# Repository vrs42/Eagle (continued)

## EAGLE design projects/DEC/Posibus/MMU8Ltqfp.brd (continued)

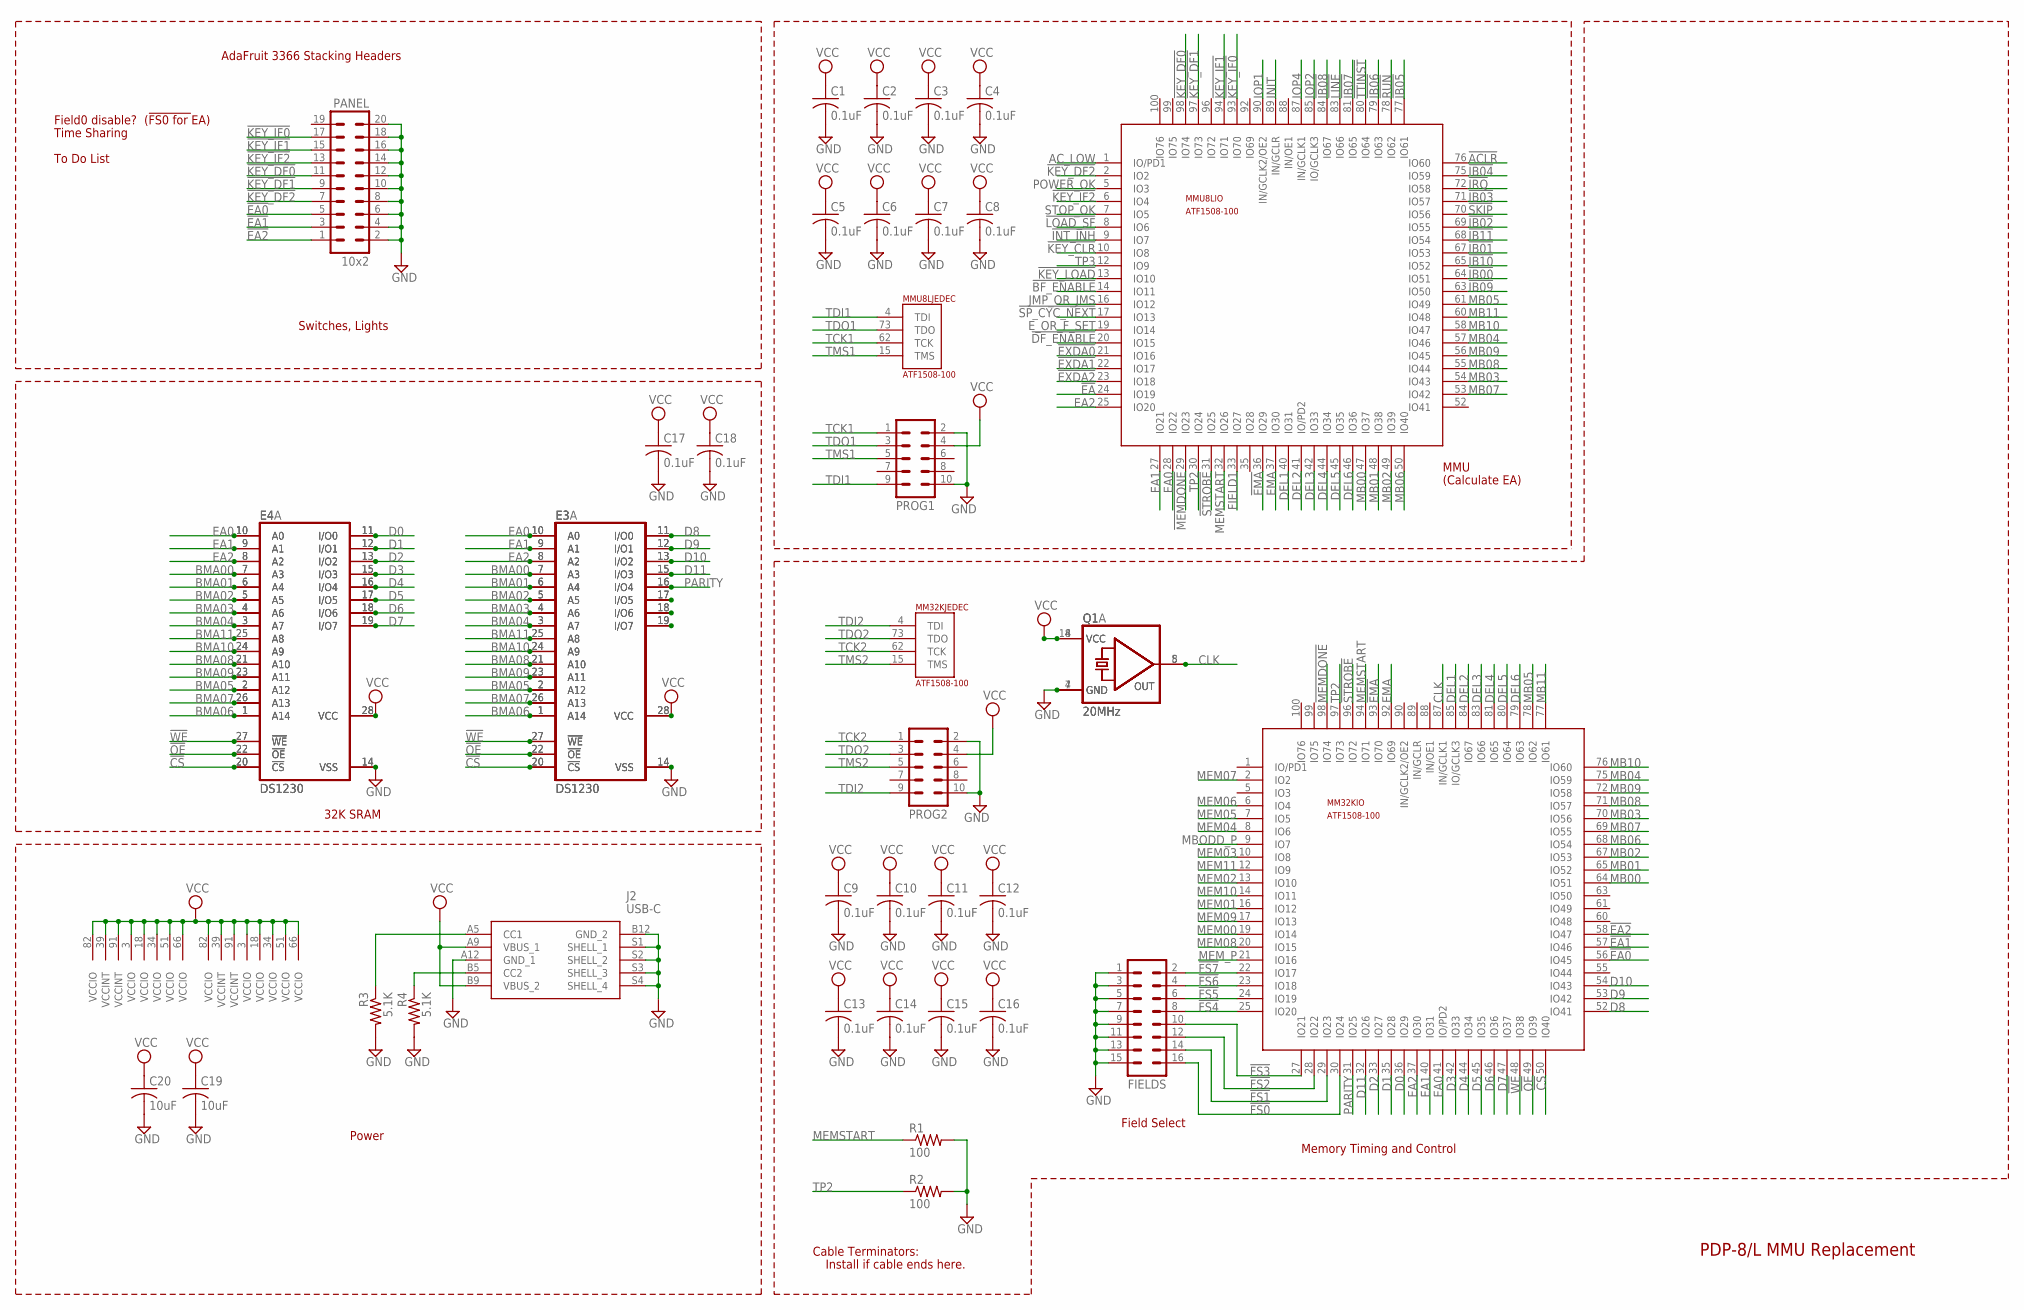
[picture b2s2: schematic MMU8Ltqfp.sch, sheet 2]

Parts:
C1, C2, C3, C4, C5, C6, C7, C8, C9, C10, C11, C12, C13, C14, C15, C16, C17, C18: 0.1uF; C0805
C19, C20: 10uF; C0805
E3, E4: DS1230; DIL28-6
E3A, E4A: DS1230; DIL28-3
FIELDS: MA08-2
J2: USB-C; USB497000A
MM32K: ATF1508-100; TQFP-100
MMU8L: ATF1508-100; TQFP-100
PANEL: 10x2; MA10-2
PROG1, PROG2: ML10
Q1: 20MHz; DIL14S
Q1A: 20MHz; DIL08S
R1, R2: 100; R1206
R3, R4: 5.1K; R0805

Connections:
!ACLR: MMU8L.76 (IO60); also elsewhere on the board
!BF_ENABLE: MMU8L.14 (IO11); also elsewhere on the board
!CS: E3.20 (!CS), E3A.20 (!CS), E4.20 (!CS), E4A.20 (!CS), MM32K.50 (IO40)
!DF_ENABLE: MMU8L.20 (IO15); also elsewhere on the board
!EA: MMU8L.24 (IO19); also elsewhere on the board
!EA0: MM32K.56 (IO45), PANEL.5
!EA1: MM32K.57 (IO46), PANEL.3
!EA2: MM32K.58 (IO47), PANEL.1
!EMA: MM32K.93 (IO70), MMU8L.36 (IO29); also elsewhere on the board
!EXDA0: MMU8L.21 (IO16); also elsewhere on the board
!EXDA1: MMU8L.22 (IO17); also elsewhere on the board
!EXDA2: MMU8L.23 (IO18); also elsewhere on the board
!FS0: FIELDS.16, MM32K.30 (IO24)
!FS1: FIELDS.14, MM32K.29 (IO23)
!FS2: FIELDS.12, MM32K.28 (IO22)
!FS3: FIELDS.10, MM32K.27 (IO21)
!FS4: FIELDS.8, MM32K.25 (IO20)
!FS5: FIELDS.6, MM32K.24 (IO19)
!FS6: FIELDS.4, MM32K.23 (IO18)
!FS7: FIELDS.2, MM32K.22 (IO17)
!IB00: MMU8L.64 (IO51); also elsewhere on the board
!IB01: MMU8L.67 (IO53); also elsewhere on the board
!IB02: MMU8L.69 (IO55); also elsewhere on the board
!IB03: MMU8L.71 (IO57); also elsewhere on the board
!IB04: MMU8L.75 (IO59); also elsewhere on the board
!IB05: MMU8L.77 (IO61); also elsewhere on the board
!IB06: MMU8L.79 (IO63); also elsewhere on the board
!IB07: MMU8L.81 (IO65); also elsewhere on the board
!IB08: MMU8L.84 (IO67); also elsewhere on the board
!IB09: MMU8L.63 (IO50); also elsewhere on the board
!IB10: MMU8L.65 (IO52); also elsewhere on the board
!IB11: MMU8L.68 (IO54); also elsewhere on the board
!INT_INH: MMU8L.9 (IO7); also elsewhere on the board
!IRQ: MMU8L.72 (IO58); also elsewhere on the board
!KEY_CLR: MMU8L.10 (IO8); also elsewhere on the board
!KEY_DF0: MMU8L.98 (IO74), PANEL.11
!KEY_DF1: MMU8L.97 (IO73), PANEL.9
!KEY_DF2: MMU8L.2 (IO2), PANEL.7; also elsewhere on the board
!KEY_IF0: MMU8L.93 (IO70), PANEL.17
!KEY_IF1: MMU8L.94 (IO71), PANEL.15
!KEY_IF2: MMU8L.6 (IO4), PANEL.13; also elsewhere on the board
!KEY_LOAD: MMU8L.13 (IO10); also elsewhere on the board
!LINE: MMU8L.83 (IO66); also elsewhere on the board
!LOAD_SF: MMU8L.8 (IO6); also elsewhere on the board
!MEMDONE: MM32K.98 (IO74), MMU8L.29 (IO23); also elsewhere on the board
!OE: E3.22 (!OE), E3A.22 (!OE), E4.22 (!OE), E4A.22 (!OE), MM32K.49 (IO39)
!RUN: MMU8L.78 (IO62); also elsewhere on the board
!SKIP: MMU8L.70 (IO56); also elsewhere on the board
!SP_CYC_NEXT: MMU8L.17 (IO13); also elsewhere on the board
!STROBE: MM32K.96 (IO72), MMU8L.31 (IO25); also elsewhere on the board
!TTINST: MMU8L.80 (IO64); also elsewhere on the board
!WE: E3.27 (!WE), E3A.27 (!WE), E4.27 (!WE), E4A.27 (!WE), MM32K.48 (IO38)
AC_LOW: MMU8L.1 (IO/PD1); also elsewhere on the board
BMA00: E3.7 (A3), E3A.7 (A3), E4.7 (A3), E4A.7 (A3); also elsewhere on the board
BMA01: E3.6 (A4), E3A.6 (A4), E4.6 (A4), E4A.6 (A4); also elsewhere on the board
BMA02: E3.5 (A5), E3A.5 (A5), E4.5 (A5), E4A.5 (A5); also elsewhere on the board
BMA03: E3.4 (A6), E3A.4 (A6), E4.4 (A6), E4A.4 (A6); also elsewhere on the board
BMA04: E3.3 (A7), E3A.3 (A7), E4.3 (A7), E4A.3 (A7); also elsewhere on the board
BMA05: E3.2 (A12), E3A.2 (A12), E4.2 (A12), E4A.2 (A12); also elsewhere on the board
BMA06: E3.1 (A14), E3A.1 (A14), E4.1 (A14), E4A.1 (A14); also elsewhere on the board
BMA07: E3.26 (A13), E3A.26 (A13), E4.26 (A13), E4A.26 (A13); also elsewhere on the board
BMA08: E3.21 (A10), E3A.21 (A10), E4.21 (A10), E4A.21 (A10); also elsewhere on the board
BMA09: E3.23 (A11), E3A.23 (A11), E4.23 (A11), E4A.23 (A11); also elsewhere on the board
BMA10: E3.24 (A9), E3A.24 (A9), E4.24 (A9), E4A.24 (A9); also elsewhere on the board
BMA11: E3.25 (A8), E3A.25 (A8), E4.25 (A8), E4A.25 (A8); also elsewhere on the board
CLK: MM32K.87 (IN/GCLK1), Q1.8 (OUT), Q1A.5 (OUT)
D0: E4.11 (I/O0), E4A.11 (I/O0), MM32K.36 (IO29)
D1: E4.12 (I/O1), E4A.12 (I/O1), MM32K.35 (IO28)
D2: E4.13 (I/O2), E4A.13 (I/O2), MM32K.33 (IO27)
D3: E4.15 (I/O3), E4A.15 (I/O3), MM32K.42 (IO33)
D4: E4.16 (I/O4), E4A.16 (I/O4), MM32K.44 (IO34)
D5: E4.17 (I/O5), E4A.17 (I/O5), MM32K.45 (IO35)
D6: E4.18 (I/O6), E4A.18 (I/O6), MM32K.46 (IO36)
D7: E4.19 (I/O7), E4A.19 (I/O7), MM32K.47 (IO37)
D8: E3.11 (I/O0), E3A.11 (I/O0), MM32K.52 (IO41)
D9: E3.12 (I/O1), E3A.12 (I/O1), MM32K.53 (IO42)
D10: E3.13 (I/O2), E3A.13 (I/O2), MM32K.54 (IO43)
D11: E3.15 (I/O3), E3A.15 (I/O3), MM32K.32 (IO26)
DEL1: MM32K.85 (IO/GCLK3), MMU8L.40 (IO31)
DEL2: MM32K.84 (IO67), MMU8L.41 (IO/PD2)
DEL3: MM32K.83 (IO66), MMU8L.42 (IO33)
DEL4: MM32K.81 (IO65), MMU8L.44 (IO34)
DEL5: MM32K.80 (IO64), MMU8L.45 (IO35)
DEL6: MM32K.79 (IO63), MMU8L.46 (IO36)
EA0: E3.10 (A0), E3A.10 (A0), E4.10 (A0), E4A.10 (A0), MM32K.41 (IO/PD2), MMU8L.28 (IO22)
EA1: E3.9 (A1), E3A.9 (A1), E4.9 (A1), E4A.9 (A1), MM32K.40 (IO31), MMU8L.27 (IO21)
EA2: E3.8 (A2), E3A.8 (A2), E4.8 (A2), E4A.8 (A2), MM32K.37 (IO30), MMU8L.25 (IO20)
EMA: MM32K.92 (IO69), MMU8L.37 (IO30); also elsewhere on the board
E_OR_F_SET: MMU8L.19 (IO14); also elsewhere on the board
FIELD1: MMU8L.33 (IO27); also elsewhere on the board
GND: C1.2, C2.2, C3.2, C4.2, C5.2, C6.2, C7.2, C8.2, C9.2, C10.2, C11.2, C12.2, C13.2, C14.2, C15.2, C16.2, C17.2, C18.2, C19.2, C20.2, E3.14 (VSS), E3A.14 (VSS), E4.14 (VSS), E4A.14 (VSS), FIELDS.1, FIELDS.3, FIELDS.5, FIELDS.7, FIELDS.9, FIELDS.11, FIELDS.13, FIELDS.15, J2.A12 (GND_1), J2.B12 (GND_2), J2.S1 (SHELL_1), J2.S2 (SHELL_2), J2.S3 (SHELL_3), J2.S4 (SHELL_4), MM32K.11 (GND), MM32K.26 (GND), MM32K.38 (GND), MM32K.43 (GND), MM32K.59 (GND), MM32K.74 (GND), MM32K.86 (GND), MM32K.95 (GND), MMU8L.11 (GND), MMU8L.26 (GND), MMU8L.38 (GND), MMU8L.43 (GND), MMU8L.59 (GND), MMU8L.74 (GND), MMU8L.86 (GND), MMU8L.95 (GND), PANEL.2, PANEL.4, PANEL.6, PANEL.8, PANEL.10, PANEL.12, PANEL.14, PANEL.16, PANEL.18, PANEL.20, PROG1.2, PROG1.10, PROG2.2, PROG2.10, Q1.7 (GND), Q1A.4 (GND), R1.2, R2.2, R3.2, R4.2; also elsewhere on the board
INIT: MMU8L.89 (IN/GCLR); also elsewhere on the board
IOP1: MMU8L.90 (IN/GCLK2/OE2); also elsewhere on the board
IOP2: MMU8L.85 (IO/GCLK3); also elsewhere on the board
IOP4: MMU8L.87 (IN/GCLK1); also elsewhere on the board
JMP_OR_JMS: MMU8L.16 (IO12); also elsewhere on the board
MB00: MM32K.64 (IO51), MMU8L.47 (IO37); also elsewhere on the board
MB01: MM32K.65 (IO52), MMU8L.48 (IO38); also elsewhere on the board
MB02: MM32K.67 (IO53), MMU8L.49 (IO39); also elsewhere on the board
MB03: MM32K.70 (IO56), MMU8L.54 (IO43); also elsewhere on the board
MB04: MM32K.75 (IO59), MMU8L.57 (IO46); also elsewhere on the board
MB05: MM32K.78 (IO62), MMU8L.61 (IO49); also elsewhere on the board
MB06: MM32K.68 (IO54), MMU8L.50 (IO40); also elsewhere on the board
MB07: MM32K.69 (IO55), MMU8L.53 (IO42); also elsewhere on the board
MB08: MM32K.71 (IO57), MMU8L.55 (IO44); also elsewhere on the board
MB09: MM32K.72 (IO58), MMU8L.56 (IO45); also elsewhere on the board
MB10: MM32K.76 (IO60), MMU8L.58 (IO47); also elsewhere on the board
MB11: MM32K.77 (IO61), MMU8L.60 (IO48); also elsewhere on the board
MBODD_P: MM32K.9 (IO7); also elsewhere on the board
MEM00: MM32K.19 (IO14); also elsewhere on the board
MEM01: MM32K.16 (IO12); also elsewhere on the board
MEM02: MM32K.13 (IO10); also elsewhere on the board
MEM03: MM32K.10 (IO8); also elsewhere on the board
MEM04: MM32K.8 (IO6); also elsewhere on the board
MEM05: MM32K.7 (IO5); also elsewhere on the board
MEM06: MM32K.6 (IO4); also elsewhere on the board
MEM07: MM32K.2 (IO2); also elsewhere on the board
MEM08: MM32K.20 (IO15); also elsewhere on the board
MEM09: MM32K.17 (IO13); also elsewhere on the board
MEM10: MM32K.14 (IO11); also elsewhere on the board
MEM11: MM32K.12 (IO9); also elsewhere on the board
MEMSTART: MM32K.94 (IO71), MMU8L.32 (IO26), R1.1; also elsewhere on the board
MEM_P: MM32K.21 (IO16); also elsewhere on the board
unnamed: J2.B5 (CC2), R4.1
unnamed: E3.17 (I/O5), E3A.17 (I/O5)
unnamed: E3.18 (I/O6), E3A.18 (I/O6)
unnamed: E3.19 (I/O7), E3A.19 (I/O7)
unnamed: J2.A5 (CC1), R3.1
PARITY: E3.16 (I/O4), E3A.16 (I/O4), MM32K.31 (IO25)
POWER_OK: MMU8L.5 (IO3); also elsewhere on the board
STOP_OK: MMU8L.7 (IO5); also elsewhere on the board
TCK1: MMU8L.62 (TCK), PROG1.1
TCK2: MM32K.62 (TCK), PROG2.1
TDI1: MMU8L.4 (TDI), PROG1.9
TDI2: MM32K.4 (TDI), PROG2.9
TDO1: MMU8L.73 (TDO), PROG1.3
TDO2: MM32K.73 (TDO), PROG2.3
TMS1: MMU8L.15 (TMS), PROG1.5
TMS2: MM32K.15 (TMS), PROG2.5
TP2: MM32K.97 (IO73), MMU8L.30 (IO24), R2.1; also elsewhere on the board
TP3: MMU8L.12 (IO9); also elsewhere on the board
VCC: C1.1, C2.1, C3.1, C4.1, C5.1, C6.1, C7.1, C8.1, C9.1, C10.1, C11.1, C12.1, C13.1, C14.1, C15.1, C16.1, C17.1, C18.1, C19.1, C20.1, E3.28 (VCC), E3A.28 (VCC), E4.28 (VCC), E4A.28 (VCC), J2.A9 (VBUS_1), J2.B9 (VBUS_2), MM32K.3 (VCCIO), MM32K.18 (VCCIO), MM32K.34 (VCCIO), MM32K.39 (VCCINT), MM32K.51 (VCCIO), MM32K.66 (VCCIO), MM32K.82 (VCCIO), MM32K.91 (VCCINT), MMU8L.3 (VCCIO), MMU8L.18 (VCCIO), MMU8L.34 (VCCIO), MMU8L.39 (VCCINT), MMU8L.51 (VCCIO), MMU8L.66 (VCCIO), MMU8L.82 (VCCIO), MMU8L.91 (VCCINT), PROG1.4, PROG2.4, Q1.14 (VCC), Q1A.8 (VCC)

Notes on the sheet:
Field Select
32K SRAM
PDP-8/L MMU Replacement
Cable Terminators:
Install if cable ends here.
Field0 disable?
Time Sharing
To Do List
(!FS0 for !EA)
AdaFruit 3366 Stacking Headers
MMU
(Calculate EA)
Memory Timing and Control
Power
Switches, Lights

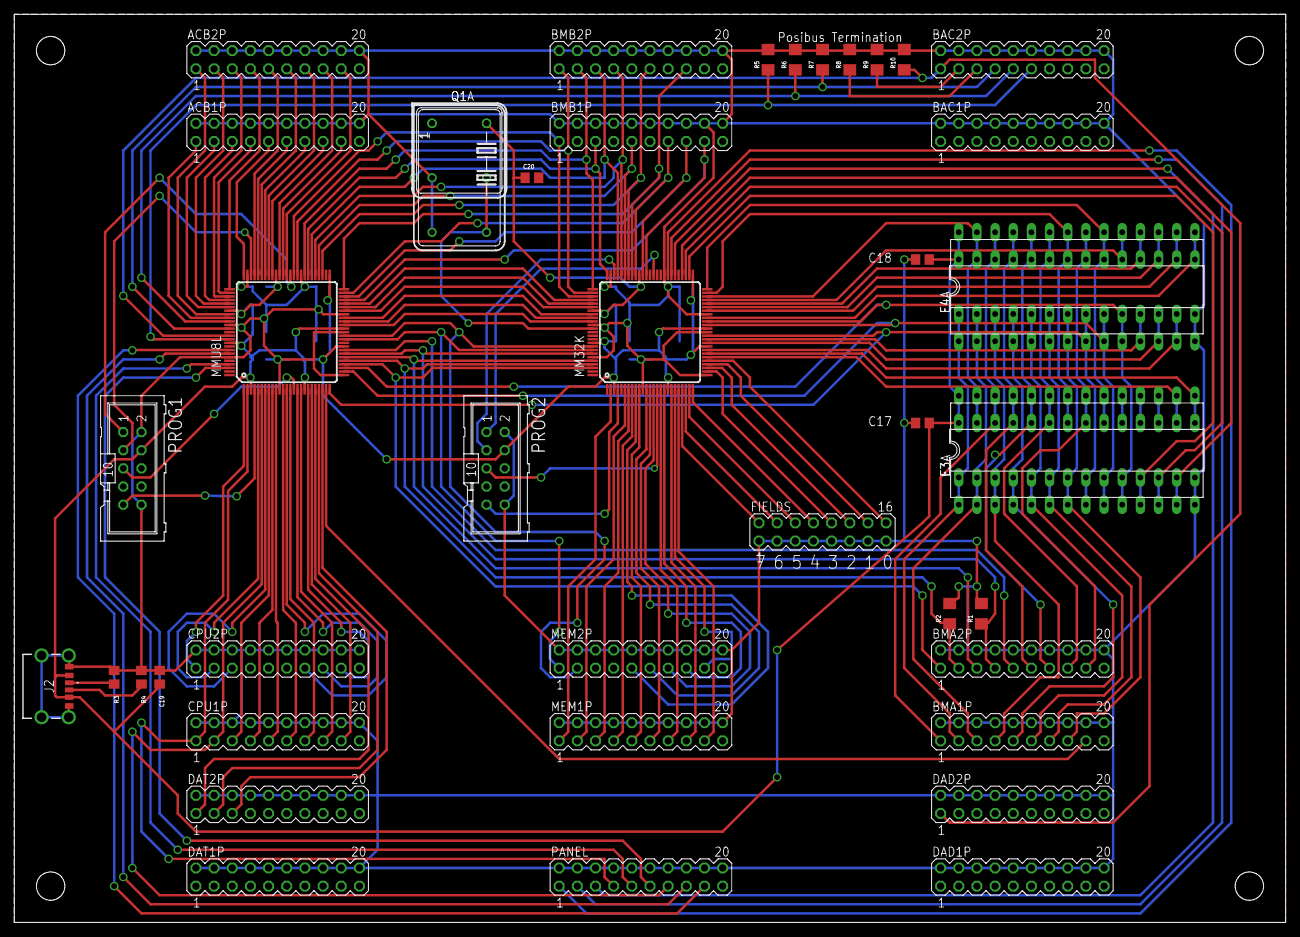
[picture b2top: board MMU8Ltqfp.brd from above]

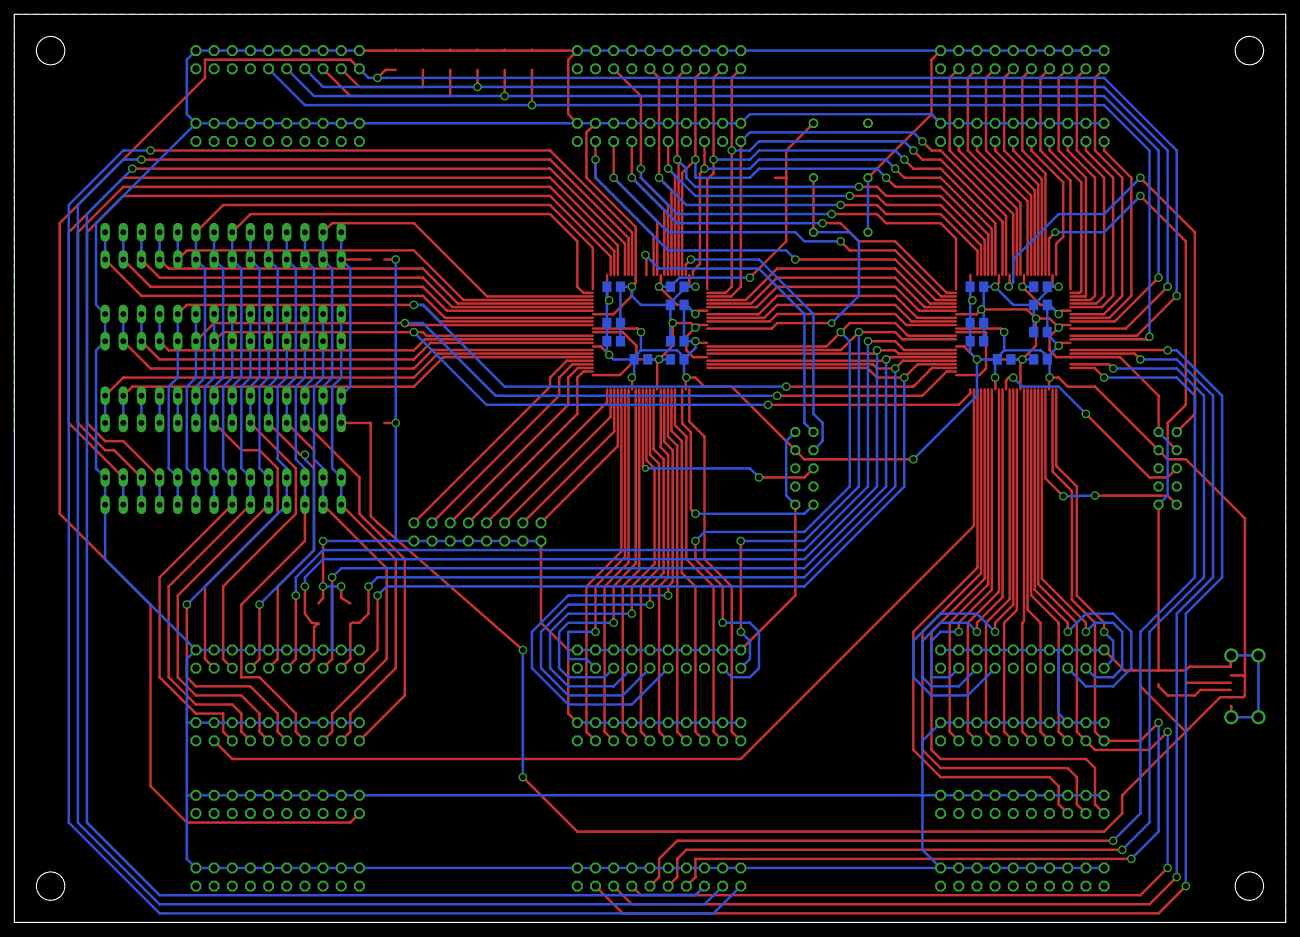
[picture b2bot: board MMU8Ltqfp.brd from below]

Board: 2 copper layers, 177.8 x 127.0 mm, 59 parts (16 on the bottom side), 144 nets.

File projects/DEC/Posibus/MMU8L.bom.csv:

Comment,Designator,Footprint,PartNo
0.1uF,C5,C0805,C5378
0.1uF,C4,C0805,C5378
0.1uF,C2,C0805,C5378
0.1uF,C17,C0805,C5378
0.1uF,C18,C0805,C5378
0.1uF,C6,C0805,C5378
0.1uF,C3,C0805,C5378
100,R1,R1206,C17901
100,R2,R1206,C17901
ATF1508-100,MMU8L,PQFP-100,C184063
ATF1508-100,MM32K,PQFP-100,C184063
0.1uF,C1,C0805,C5378
0.1uF,C7,C0805,C5378
0.1uF,C8,C0805,C5378
0.1uF,C13,C0805,C5378
0.1uF,C12,C0805,C5378
0.1uF,C10,C0805,C5378
0.1uF,C14,C0805,C5378
0.1uF,C11,C0805,C5378
0.1uF,C9,C0805,C5378
0.1uF,C15,C0805,C5378
0.1uF,C16,C0805,C5378
5.1K,R4,R0805,C27834
5.1K,R3,R0805,C27834
100,R5,R1206,C17901
100,R6,R1206,C17901
100,R7,R1206,C17901
100,R8,R1206,C17901
100,R9,R1206,C17901
100,R10,R1206,C17901
10uF,C19,C0805,C15850
10uF,C20,C0805,C15850

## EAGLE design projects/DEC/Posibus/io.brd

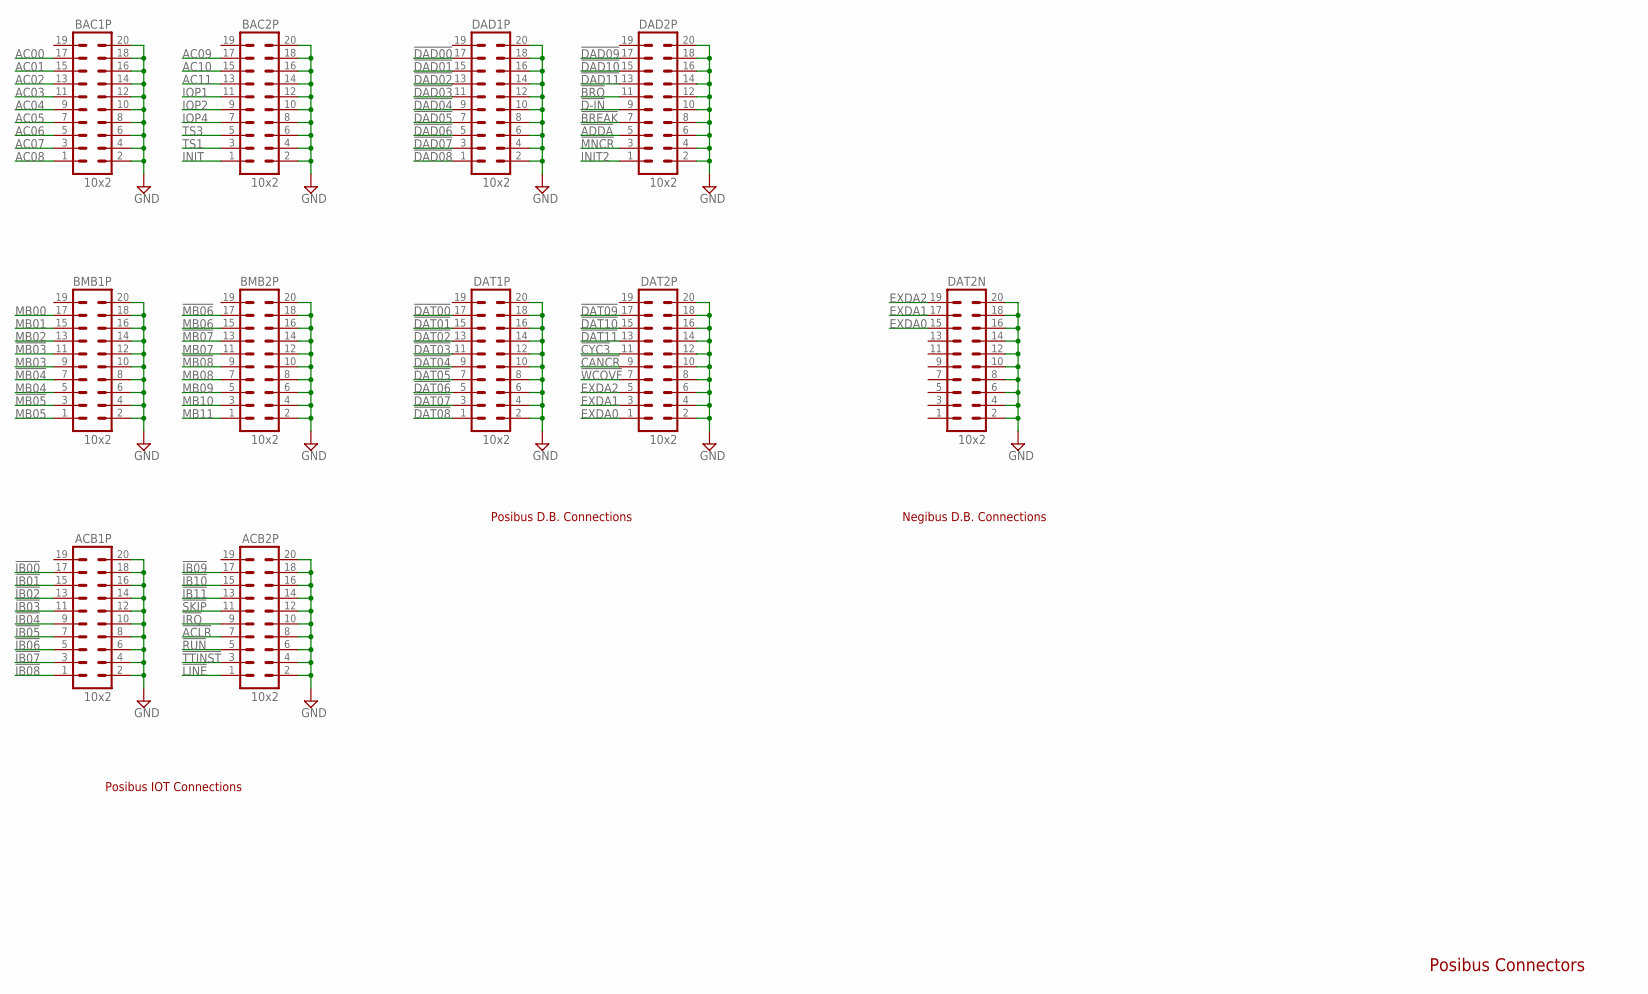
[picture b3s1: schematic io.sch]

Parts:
ACB1P, ACB2P: 10x2; MA10-2
BAC1P, BAC2P: 10x2; MA10-2
BMB1P, BMB2P: 10x2; MA10-2
DAD1P, DAD2P: 10x2; MA10-2
DAT1P, DAT2N, DAT2P: 10x2; MA10-2

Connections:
!ACLR: ACB2P.7
!ADDA: DAD2P.5
!BREAK: DAD2P.7
!BRQ: DAD2P.11
!CANCR: DAT2P.9
!CYC3: DAT2P.11
!D-IN: DAD2P.9
!DAD00: DAD1P.17
!DAD01: DAD1P.15
!DAD02: DAD1P.13
!DAD03: DAD1P.11
!DAD04: DAD1P.9
!DAD05: DAD1P.7
!DAD06: DAD1P.5
!DAD07: DAD1P.3
!DAD08: DAD1P.1
!DAD09: DAD2P.17
!DAD10: DAD2P.15
!DAD11: DAD2P.13
!DAT00: DAT1P.17
!DAT01: DAT1P.15
!DAT02: DAT1P.13
!DAT03: DAT1P.11
!DAT04: DAT1P.9
!DAT05: DAT1P.7
!DAT06: DAT1P.5
!DAT07: DAT1P.3
!DAT08: DAT1P.1
!DAT09: DAT2P.17
!DAT10: DAT2P.15
!DAT11: DAT2P.13
!IB00: ACB1P.17
!IB01: ACB1P.15
!IB02: ACB1P.13
!IB03: ACB1P.11
!IB04: ACB1P.9
!IB05: ACB1P.7
!IB06: ACB1P.5
!IB07: ACB1P.3
!IB08: ACB1P.1
!IB09: ACB2P.17
!IB10: ACB2P.15
!IB11: ACB2P.13
!IRQ: ACB2P.9
!LINE: ACB2P.1
!MB03: BMB1P.11
!MB04: BMB1P.7
!MB05: BMB1P.3
!MB06: BMB2P.17
!MB07: BMB2P.13
!MB08: BMB2P.9
!MNCR: DAD2P.3
!RUN: ACB2P.5
!SKIP: ACB2P.11
!TTINST: ACB2P.3
!WCOVF: DAT2P.7
AC00: BAC1P.17
AC01: BAC1P.15
AC02: BAC1P.13
AC03: BAC1P.11
AC04: BAC1P.9
AC05: BAC1P.7
AC06: BAC1P.5
AC07: BAC1P.3
AC08: BAC1P.1
AC09: BAC2P.17
AC10: BAC2P.15
AC11: BAC2P.13
EXDA0: DAT2N.15, DAT2P.1
EXDA1: DAT2N.17, DAT2P.3
EXDA2: DAT2N.19, DAT2P.5
GND: ACB1P.2, ACB1P.4, ACB1P.6, ACB1P.8, ACB1P.10, ACB1P.12, ACB1P.14, ACB1P.16, ACB1P.18, ACB1P.20, ACB2P.2, ACB2P.4, ACB2P.6, ACB2P.8, ACB2P.10, ACB2P.12, ACB2P.14, ACB2P.16, ACB2P.18, ACB2P.20, BAC1P.2, BAC1P.4, BAC1P.6, BAC1P.8, BAC1P.10, BAC1P.12, BAC1P.14, BAC1P.16, BAC1P.18, BAC1P.20, BAC2P.2, BAC2P.4, BAC2P.6, BAC2P.8, BAC2P.10, BAC2P.12, BAC2P.14, BAC2P.16, BAC2P.18, BAC2P.20, BMB1P.2, BMB1P.4, BMB1P.6, BMB1P.8, BMB1P.10, BMB1P.12, BMB1P.14, BMB1P.16, BMB1P.18, BMB1P.20, BMB2P.2, BMB2P.4, BMB2P.6, BMB2P.8, BMB2P.10, BMB2P.12, BMB2P.14, BMB2P.16, BMB2P.18, BMB2P.20, DAD1P.2, DAD1P.4, DAD1P.6, DAD1P.8, DAD1P.10, DAD1P.12, DAD1P.14, DAD1P.16, DAD1P.18, DAD1P.20, DAD2P.2, DAD2P.4, DAD2P.6, DAD2P.8, DAD2P.10, DAD2P.12, DAD2P.14, DAD2P.16, DAD2P.18, DAD2P.20, DAT1P.2, DAT1P.4, DAT1P.6, DAT1P.8, DAT1P.10, DAT1P.12, DAT1P.14, DAT1P.16, DAT1P.18, DAT1P.20, DAT2N.2, DAT2N.4, DAT2N.6, DAT2N.8, DAT2N.10, DAT2N.12, DAT2N.14, DAT2N.16, DAT2N.18, DAT2N.20, DAT2P.2, DAT2P.4, DAT2P.6, DAT2P.8, DAT2P.10, DAT2P.12, DAT2P.14, DAT2P.16, DAT2P.18, DAT2P.20
INIT: BAC2P.1
INIT2: DAD2P.1
IOP1: BAC2P.11
IOP2: BAC2P.9
IOP4: BAC2P.7
MB00: BMB1P.17
MB01: BMB1P.15
MB02: BMB1P.13
MB03: BMB1P.9
MB04: BMB1P.5
MB05: BMB1P.1
MB06: BMB2P.15
MB07: BMB2P.11
MB08: BMB2P.7
MB09: BMB2P.5
MB10: BMB2P.3
MB11: BMB2P.1
TS1: BAC2P.3
TS3: BAC2P.5

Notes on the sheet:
Posibus IOT Connections
Posibus D.B. Connections
Posibus Connectors
Negibus D.B. Connections

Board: 2 copper layers, 11 parts (0 on the bottom side), 4 nets, no tracks yet.

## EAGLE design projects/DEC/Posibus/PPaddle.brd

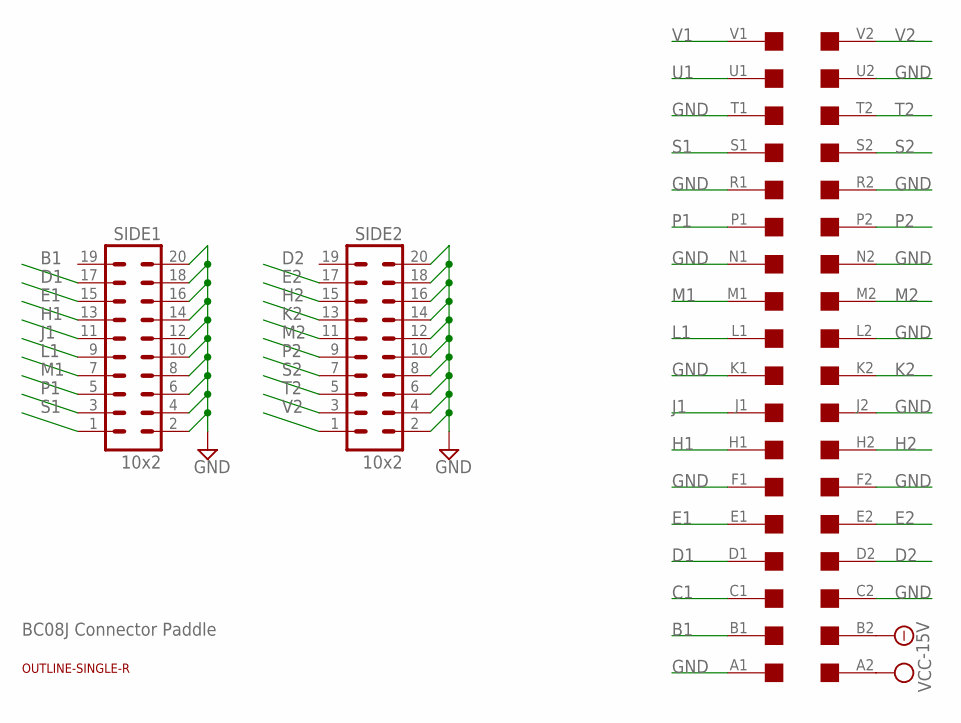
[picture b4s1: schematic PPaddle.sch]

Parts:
SIDE1, SIDE2: 10x2; 20H
U$1: OUTLINE-SINGLE-R; SINGLE-R
U$2: EDGE; EDGE-CON2

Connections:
-15V: U$2.B2
B1: SIDE1.17, U$2.B1
C1: U$2.C1
D1: SIDE1.15, U$2.D1
D2: SIDE2.17, U$2.D2
E1: SIDE1.13, U$2.E1
E2: SIDE2.15, U$2.E2
GND: SIDE1.2, SIDE1.4, SIDE1.6, SIDE1.8, SIDE1.10, SIDE1.12, SIDE1.14, SIDE1.16, SIDE1.18, SIDE1.20, SIDE2.2, SIDE2.4, SIDE2.6, SIDE2.8, SIDE2.10, SIDE2.12, SIDE2.14, SIDE2.16, SIDE2.18, SIDE2.20, U$2.A1, U$2.C2, U$2.F1, U$2.F2, U$2.J2, U$2.K1, U$2.L2, U$2.N1, U$2.N2, U$2.R1, U$2.R2, U$2.T1, U$2.U2
H1: SIDE1.11, U$2.H1
H2: SIDE2.13, U$2.H2
J1: SIDE1.9, U$2.J1
K2: SIDE2.11, U$2.K2
L1: SIDE1.7, U$2.L1
M1: SIDE1.5, U$2.M1
M2: SIDE2.9, U$2.M2
P1: SIDE1.3, U$2.P1
P2: SIDE2.7, U$2.P2
S1: SIDE1.1, U$2.S1
S2: SIDE2.5, U$2.S2
T2: SIDE2.3, U$2.T2
U1: U$2.U1
V1: U$2.V1
V2: SIDE2.1, U$2.V2
VCC: U$2.A2

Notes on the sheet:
BC08J Connector Paddle

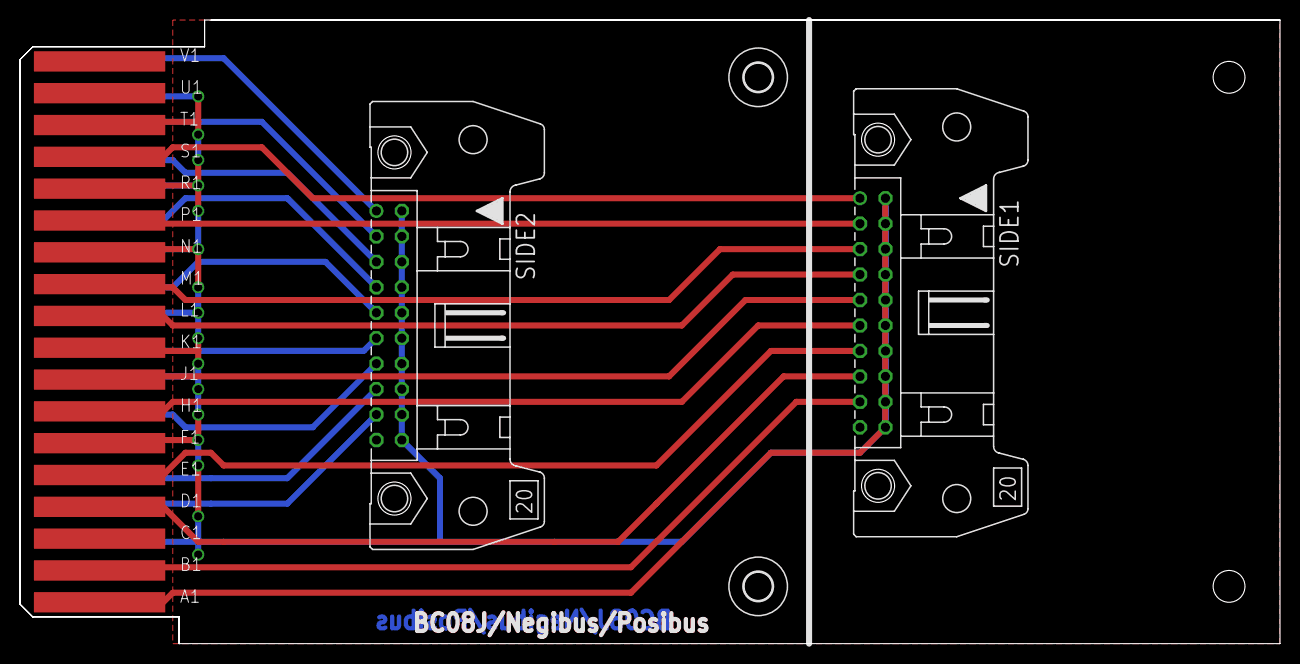
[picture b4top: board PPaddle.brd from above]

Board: 2 copper layers, 125.7 x 62.2 mm, 6 parts (0 on the bottom side), 19 nets.

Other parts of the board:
U$3, U$4: 2,8

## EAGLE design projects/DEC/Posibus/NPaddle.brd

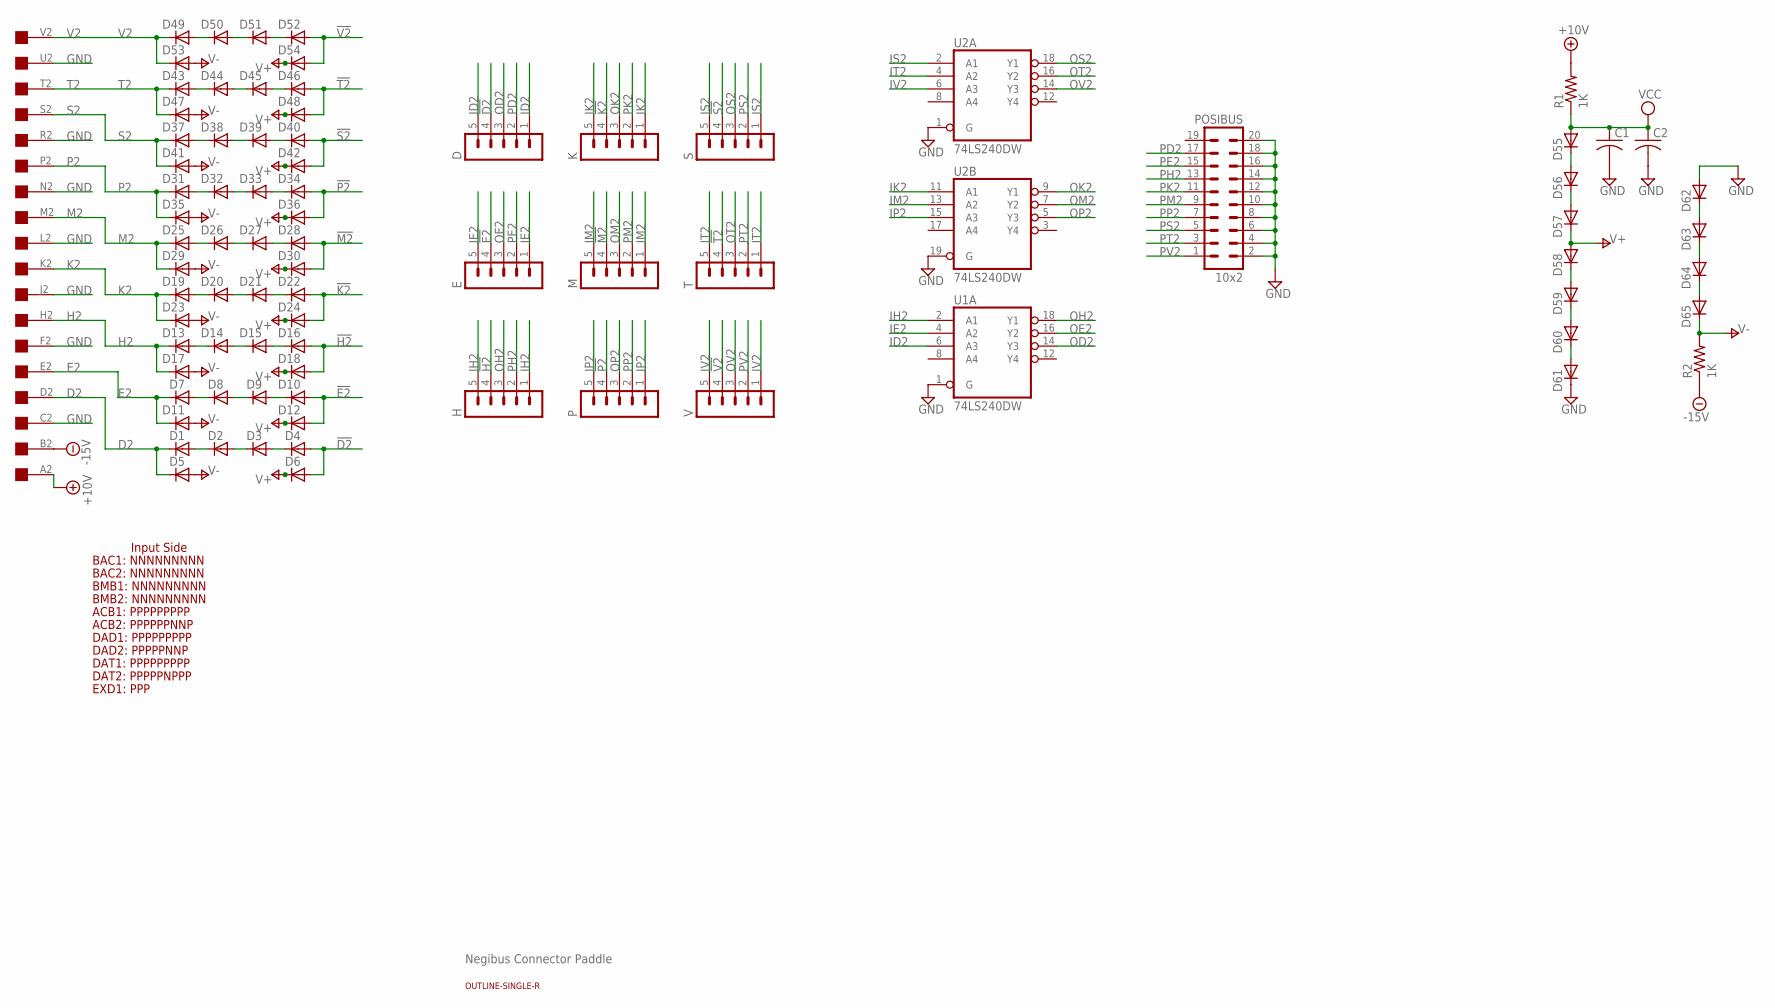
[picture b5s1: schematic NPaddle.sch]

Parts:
C1, C2: C050-025X075
D: MA05-1
D1, D2, D3, D4, D5, D6, D7, D8, D9, D10, D11, D12, D13, D14, D15, D16, D17, D18, D19, D20, D21, D22, D23, D24, D25, D26, D27, D28, D29, D30, D31, D32, D33, D34, D35, D36, D37, D38, D39, D40, D41, D42, D43, D44, D45, D46, D47, D48, D49, D50, D51, D52, D53, D54, D55, D56, D57, D58, D59, D60, D61, D62, D63, D64, D65: 1N4148WS; SOD323-W
E: MA05-1
H: MA05-1
K: MA05-1
M: MA05-1
P: MA05-1
POSIBUS: 10x2; MA10-2
R1, R2: 1K; 0207/10
S: MA05-1
T: MA05-1
U1, U2: 74LS240DW; SO20W
U$1: OUTLINE-SINGLE-R; SINGLE-R
U$2: EDGE; EDGE-CON2
V: MA05-1

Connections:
!D2: D.4, D4.A, D6.A
!E2: D10.A, D12.A, E.4
!H2: D16.A, D18.A, H.4
!K2: D22.A, D24.A, K.4
!M2: D28.A, D30.A, M.4
!P2: D34.A, D36.A, P.4
!S2: D40.A, D42.A, S.4
!T2: D46.A, D48.A, T.4
!V2: D52.A, D54.A, V.4
+10V: R1.2, U$2.A2
-15V: R2.1, U$2.B2
D2: D1.C, D5.C, U$2.D2
E2: D7.C, D11.C, U$2.E2
GND: C1.2, C2.2, D61.C, D62.A, POSIBUS.2, POSIBUS.4, POSIBUS.6, POSIBUS.8, POSIBUS.10, POSIBUS.12, POSIBUS.14, POSIBUS.16, POSIBUS.18, POSIBUS.20, U1.1 (G), U1.10 (GND), U2.1 (G), U2.10 (GND), U2.19 (G), U$2.C2, U$2.F2, U$2.J2, U$2.L2, U$2.N2, U$2.R2, U$2.U2
H2: D13.C, D17.C, U$2.H2
ID2: D.1, D.5, U1.6 (A3)
IE2: E.1, E.5, U1.4 (A2)
IH2: H.1, H.5, U1.2 (A1)
IK2: K.1, K.5, U2.11 (A1)
IM2: M.1, M.5, U2.13 (A2)
IP2: P.1, P.5, U2.15 (A3)
IS2: S.1, S.5, U2.2 (A1)
IT2: T.1, T.5, U2.4 (A2)
IV2: U2.6 (A3), V.1, V.5
K2: D19.C, D23.C, U$2.K2
M2: D25.C, D29.C, U$2.M2
unnamed: D13.A, D14.C
unnamed: D1.A, D2.C
unnamed: D2.A, D3.C
unnamed: D3.A, D4.C
unnamed: D14.A, D15.C
unnamed: D15.A, D16.C
unnamed: D7.A, D8.C
unnamed: D8.A, D9.C
unnamed: D9.A, D10.C
unnamed: D19.A, D20.C
unnamed: D20.A, D21.C
unnamed: D21.A, D22.C
unnamed: D25.A, D26.C
unnamed: D26.A, D27.C
unnamed: D27.A, D28.C
unnamed: D31.A, D32.C
unnamed: D32.A, D33.C
unnamed: D33.A, D34.C
unnamed: D37.A, D38.C
unnamed: D38.A, D39.C
unnamed: D39.A, D40.C
unnamed: D43.A, D44.C
unnamed: D44.A, D45.C
unnamed: D45.A, D46.C
unnamed: D49.A, D50.C
unnamed: D50.A, D51.C
unnamed: D51.A, D52.C
unnamed: D55.C, D56.A
unnamed: D56.C, D57.A
unnamed: D62.C, D63.A
unnamed: D58.C, D59.A
unnamed: D59.C, D60.A
unnamed: D60.C, D61.A
unnamed: D63.C, D64.A
unnamed: D64.C, D65.A
OD2: D.3, U1.14 (Y3)
OE2: E.3, U1.16 (Y2)
OH2: H.3, U1.18 (Y1)
OK2: K.3, U2.9 (Y1)
OM2: M.3, U2.7 (Y2)
OP2: P.3, U2.5 (Y3)
OS2: S.3, U2.18 (Y1)
OT2: T.3, U2.16 (Y2)
OV2: U2.14 (Y3), V.3
P2: D31.C, D35.C, U$2.P2
PD2: D.2, POSIBUS.17
PE2: E.2, POSIBUS.15
PH2: H.2, POSIBUS.13
PK2: K.2, POSIBUS.11
PM2: M.2, POSIBUS.9
PP2: P.2, POSIBUS.7
PS2: POSIBUS.5, S.2
PT2: POSIBUS.3, T.2
PV2: POSIBUS.1, V.2
S2: D37.C, D41.C, U$2.S2
T2: D43.C, D47.C, U$2.T2
V2: D49.C, D53.C, U$2.V2
V+: D6.C, D12.C, D18.C, D24.C, D30.C, D36.C, D42.C, D48.C, D54.C, D57.C, D58.A
V-: D5.A, D11.A, D17.A, D23.A, D29.A, D35.A, D41.A, D47.A, D53.A, D65.C, R2.2
VCC: C1.1, C2.1, D55.A, R1.1, U1.20 (VCC), U2.20 (VCC)

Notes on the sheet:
Negibus Connector Paddle
BAC1: NNNNNNNNN
Input Side
BAC2: NNNNNNNNN
BMB1: NNNNNNNNN
BMB2: NNNNNNNNN
ACB1: PPPPPPPPP
ACB2: PPPPPPNNP
DAD1: PPPPPPPPP
DAD2: PPPPPNNP
DAT1: PPPPPPPPP
DAT2: PPPPPNPPP
EXD1: PPP

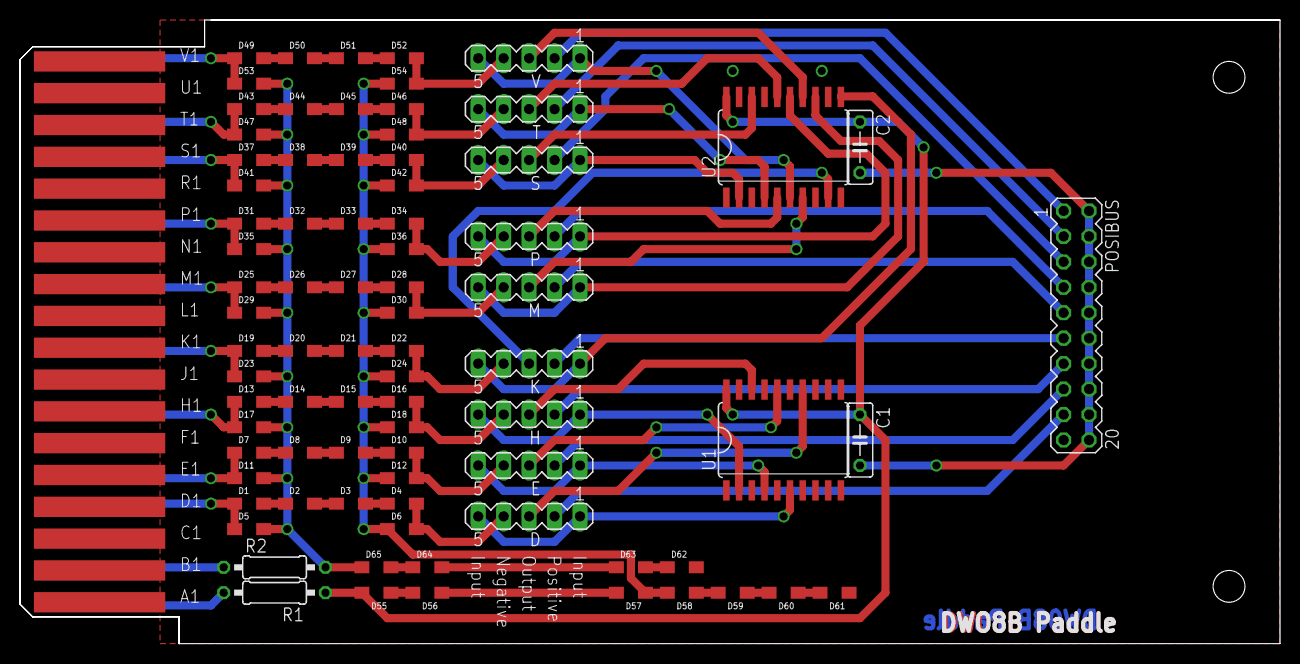
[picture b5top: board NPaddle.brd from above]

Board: 2 copper layers, 125.7 x 62.2 mm, 83 parts (0 on the bottom side), 86 nets.

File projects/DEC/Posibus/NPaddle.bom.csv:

Comment,Designator,Footprint,PartNo
1N4148WS,D1,SOD323-W,C2128
1N4148WS,D2,SOD323-W,C2128
1N4148WS,D3,SOD323-W,C2128
1N4148WS,D4,SOD323-W,C2128
1N4148WS,D5,SOD323-W,C2128
1N4148WS,D6,SOD323-W,C2128
1N4148WS,D7,SOD323-W,C2128
1N4148WS,D8,SOD323-W,C2128
1N4148WS,D9,SOD323-W,C2128
1N4148WS,D10,SOD323-W,C2128
1N4148WS,D11,SOD323-W,C2128
1N4148WS,D12,SOD323-W,C2128
1N4148WS,D13,SOD323-W,C2128
1N4148WS,D14,SOD323-W,C2128
1N4148WS,D15,SOD323-W,C2128
1N4148WS,D16,SOD323-W,C2128
1N4148WS,D17,SOD323-W,C2128
1N4148WS,D18,SOD323-W,C2128
1N4148WS,D19,SOD323-W,C2128
1N4148WS,D20,SOD323-W,C2128
1N4148WS,D21,SOD323-W,C2128
1N4148WS,D22,SOD323-W,C2128
1N4148WS,D23,SOD323-W,C2128
1N4148WS,D24,SOD323-W,C2128
1N4148WS,D25,SOD323-W,C2128
1N4148WS,D26,SOD323-W,C2128
1N4148WS,D27,SOD323-W,C2128
1N4148WS,D28,SOD323-W,C2128
1N4148WS,D29,SOD323-W,C2128
1N4148WS,D30,SOD323-W,C2128
1N4148WS,D31,SOD323-W,C2128
1N4148WS,D32,SOD323-W,C2128
1N4148WS,D33,SOD323-W,C2128
1N4148WS,D34,SOD323-W,C2128
1N4148WS,D35,SOD323-W,C2128
1N4148WS,D36,SOD323-W,C2128
1N4148WS,D37,SOD323-W,C2128
1N4148WS,D38,SOD323-W,C2128
1N4148WS,D39,SOD323-W,C2128
1N4148WS,D40,SOD323-W,C2128
1N4148WS,D41,SOD323-W,C2128
1N4148WS,D42,SOD323-W,C2128
1N4148WS,D43,SOD323-W,C2128
1N4148WS,D44,SOD323-W,C2128
1N4148WS,D45,SOD323-W,C2128
1N4148WS,D46,SOD323-W,C2128
1N4148WS,D47,SOD323-W,C2128
1N4148WS,D48,SOD323-W,C2128
1N4148WS,D49,SOD323-W,C2128
1N4148WS,D50,SOD323-W,C2128
1N4148WS,D51,SOD323-W,C2128
1N4148WS,D52,SOD323-W,C2128
1N4148WS,D53,SOD323-W,C2128
1N4148WS,D54,SOD323-W,C2128
74LS240DW,U2,SO20W,C22449636
74LS240DW,U1,SO20W,C22449636
1N4148WS,D55,SOD323-W,C2128
1N4148WS,D56,SOD323-W,C2128
1N4148WS,D57,SOD323-W,C2128
1N4148WS,D58,SOD323-W,C2128
1N4148WS,D59,SOD323-W,C2128
1N4148WS,D60,SOD323-W,C2128
1N4148WS,D61,SOD323-W,C2128
1N4148WS,D62,SOD323-W,C2128
1N4148WS,D63,SOD323-W,C2128
1N4148WS,D64,SOD323-W,C2128
1N4148WS,D65,SOD323-W,C2128
